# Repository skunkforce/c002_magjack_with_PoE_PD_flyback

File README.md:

# edgy_board number c002
This design is part of the [edgy board project](https://github.com/skunkforce/edgy_boards). It provides a unified PoE flyback with magjack which can be added to c001 to provide a complete system. 

# getting started
This repository uses submodules. After cloning use the command 

```$ git submodule update --init --recursive```

to pull the submodules before opening the project with kicad. 

# Tests
Tests can be found in [TESTS.md](TESTS.md)

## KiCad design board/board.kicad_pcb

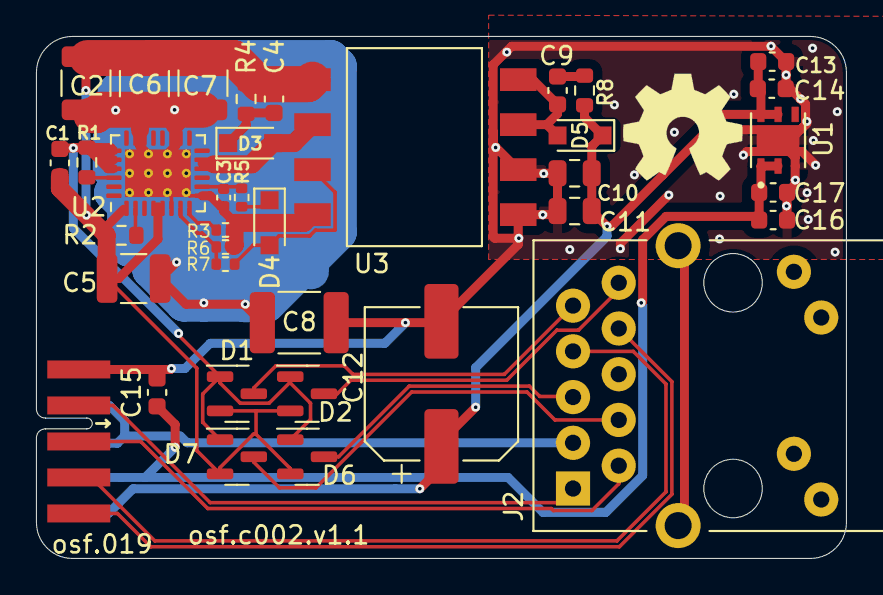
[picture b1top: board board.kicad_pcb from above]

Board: 2 copper layers, 45.0 x 29.0 mm, 38 parts (0 on the bottom side), 26 nets.

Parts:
C1: 100nF; C_0603_1608Metric
C2, C5, C6, C7: 2.2uF; C_1210_3225Metric
C3: 100nF; C_0402_1005Metric
C4, C9: 10nF; C_0603_1608Metric
C8: 1nF; C_1812_4532Metric
C10, C11: 22uF; C_0805_2012Metric
C12: 220uF; CP_Elec_8x6.9
C13, C17: 1uF; C_0603_1608Metric
C14, C15, C16: 10uF; C_0603_1608Metric
D1, D2, D6, D7: BAV99; SOT-23
D3: BAV21WS-HE3-18; D_SOD-323_HandSoldering
D4: 1N4148; D_SOD-323_HandSoldering
D5: CUS15S30,H3F; D_SOD-323_HandSoldering
J1: 019_100BASE-T_with_CT; on_edge_2x05_device
J2: LPJ4265BDNL
LOGO1: Logo_Open_Hardware_Small; OSHW-Symbol_6.7x6mm_SilkScreen
R1: 41.2R; R_0603_1608Metric
R2: 24.9k; R_0603_1608Metric
R3: 316k; R_0402_1005Metric
R4: 10k; R_0603_1608Metric
R5: 5k; R_0402_1005Metric
R6: 20k; R_0402_1005Metric
R7: 121k; R_0402_1005Metric
R8: 20R; R_0603_1608Metric
U1: LD39200PU33R; SON95P300X300X100-7N
U2: MP8007; QFN-28-1EP_4x5mm_P0.5mm_EP2.65x3.65mm_ThermalVias
U3: POE30P-50L; Transformer_Coilcraft_POE30P

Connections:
/Controller/5V: C10.1, C11.1, C12.1, C13.1, C14.1, D5.1 (K), J1.10 (5V), R8.2, U1.5 (EN), U1.6 (IN)
/Controller/GNDPWR: C2.2, C3.2, C5.2, C6.2, C7.2, C8.2, R3.2, R6.1, U2.6 (MODE), U2.9 (AGND), U2.16 (GND), U2.17, U2.20 (RTN), U2.21, U2.29 (GND), U3.1 (B-)
/Controller/PoE+: C1.1, C2.1, C4.2, C5.1, C6.1, C7.1, D1.2 (A), D2.2 (A), D6.2 (A), D7.2 (A), R2.1, R4.2, U2.1 (AUX), U2.4 (VDD), U2.5 (FB2), U3.4 (P-)
/Controller/PoE-: C1.2, D1.1 (K), D2.1 (K), D6.1 (K), D7.1 (K), R1.2, U2.23 (VSS), U2.24, U2.25 (FTY)
/ldo/3.3v: C15.1, C16.1, C17.1, J1.9 (3.3V), U1.1 (OUT), U1.2 (SENSE)
/magjack/CT: J1.7 (CT1), J1.8 (CT2), J2.3 (CT)
/magjack/CT1: D1.3 (K), J2.9
/magjack/CT2: D2.3 (K), J2.10
/magjack/CT3: D6.3 (K), J2.5
/magjack/CT4: D7.3 (K), J2.4
/magjack/RX+: J1.4 (TD2+), J2.7 (RD+)
/magjack/RX-: J1.5 (TD2-), J2.8 (RD-)
/magjack/TX+: J1.2 (TD1+), J2.1 (TD+)
/magjack/TX-: J1.3 (TD1-), J2.2 (TD-)
GND: C8.1, C10.2, C11.2, C12.2, C13.2, C14.2, C15.2, C16.2, C17.2, J1.1 (GND), J1.6 (GND), U1.3 (GND), U1.7 (EXP), U3.7 (S2-), U3.8 (S-)
unnamed: C9.2, R8.1
unnamed: D3.2 (A), U2.12 (SW), U2.13, U3.3 (P+)
unnamed: C4.1, D3.1 (K), R4.1
unnamed: D4.2 (A), R7.1, U3.2 (B+)
unnamed: D4.1 (K), R5.1
unnamed: C9.1, D5.2 (A), U3.5 (S2+), U3.6 (S+)
unnamed: R1.1, U2.26 (CLASS)
unnamed: R2.2, U2.2 (DET)
unnamed: R6.2, R7.2, U2.7 (FB1)
unnamed: R3.1, U2.8 (ILIM)
unnamed: C3.1, R5.2, U2.10 (VCC)

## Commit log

2023-05-27 initial
2023-05-28 cleaned up silkscreen
2023-11-28 added LDO
2023-12-18 tuned ILIM resistor and voltage divider of flyback
2023-12-20 made bulk cap footprint larger
2023-12-21 improved docs for D4
2024-01-05 added pours for LDO and LCSC parts
